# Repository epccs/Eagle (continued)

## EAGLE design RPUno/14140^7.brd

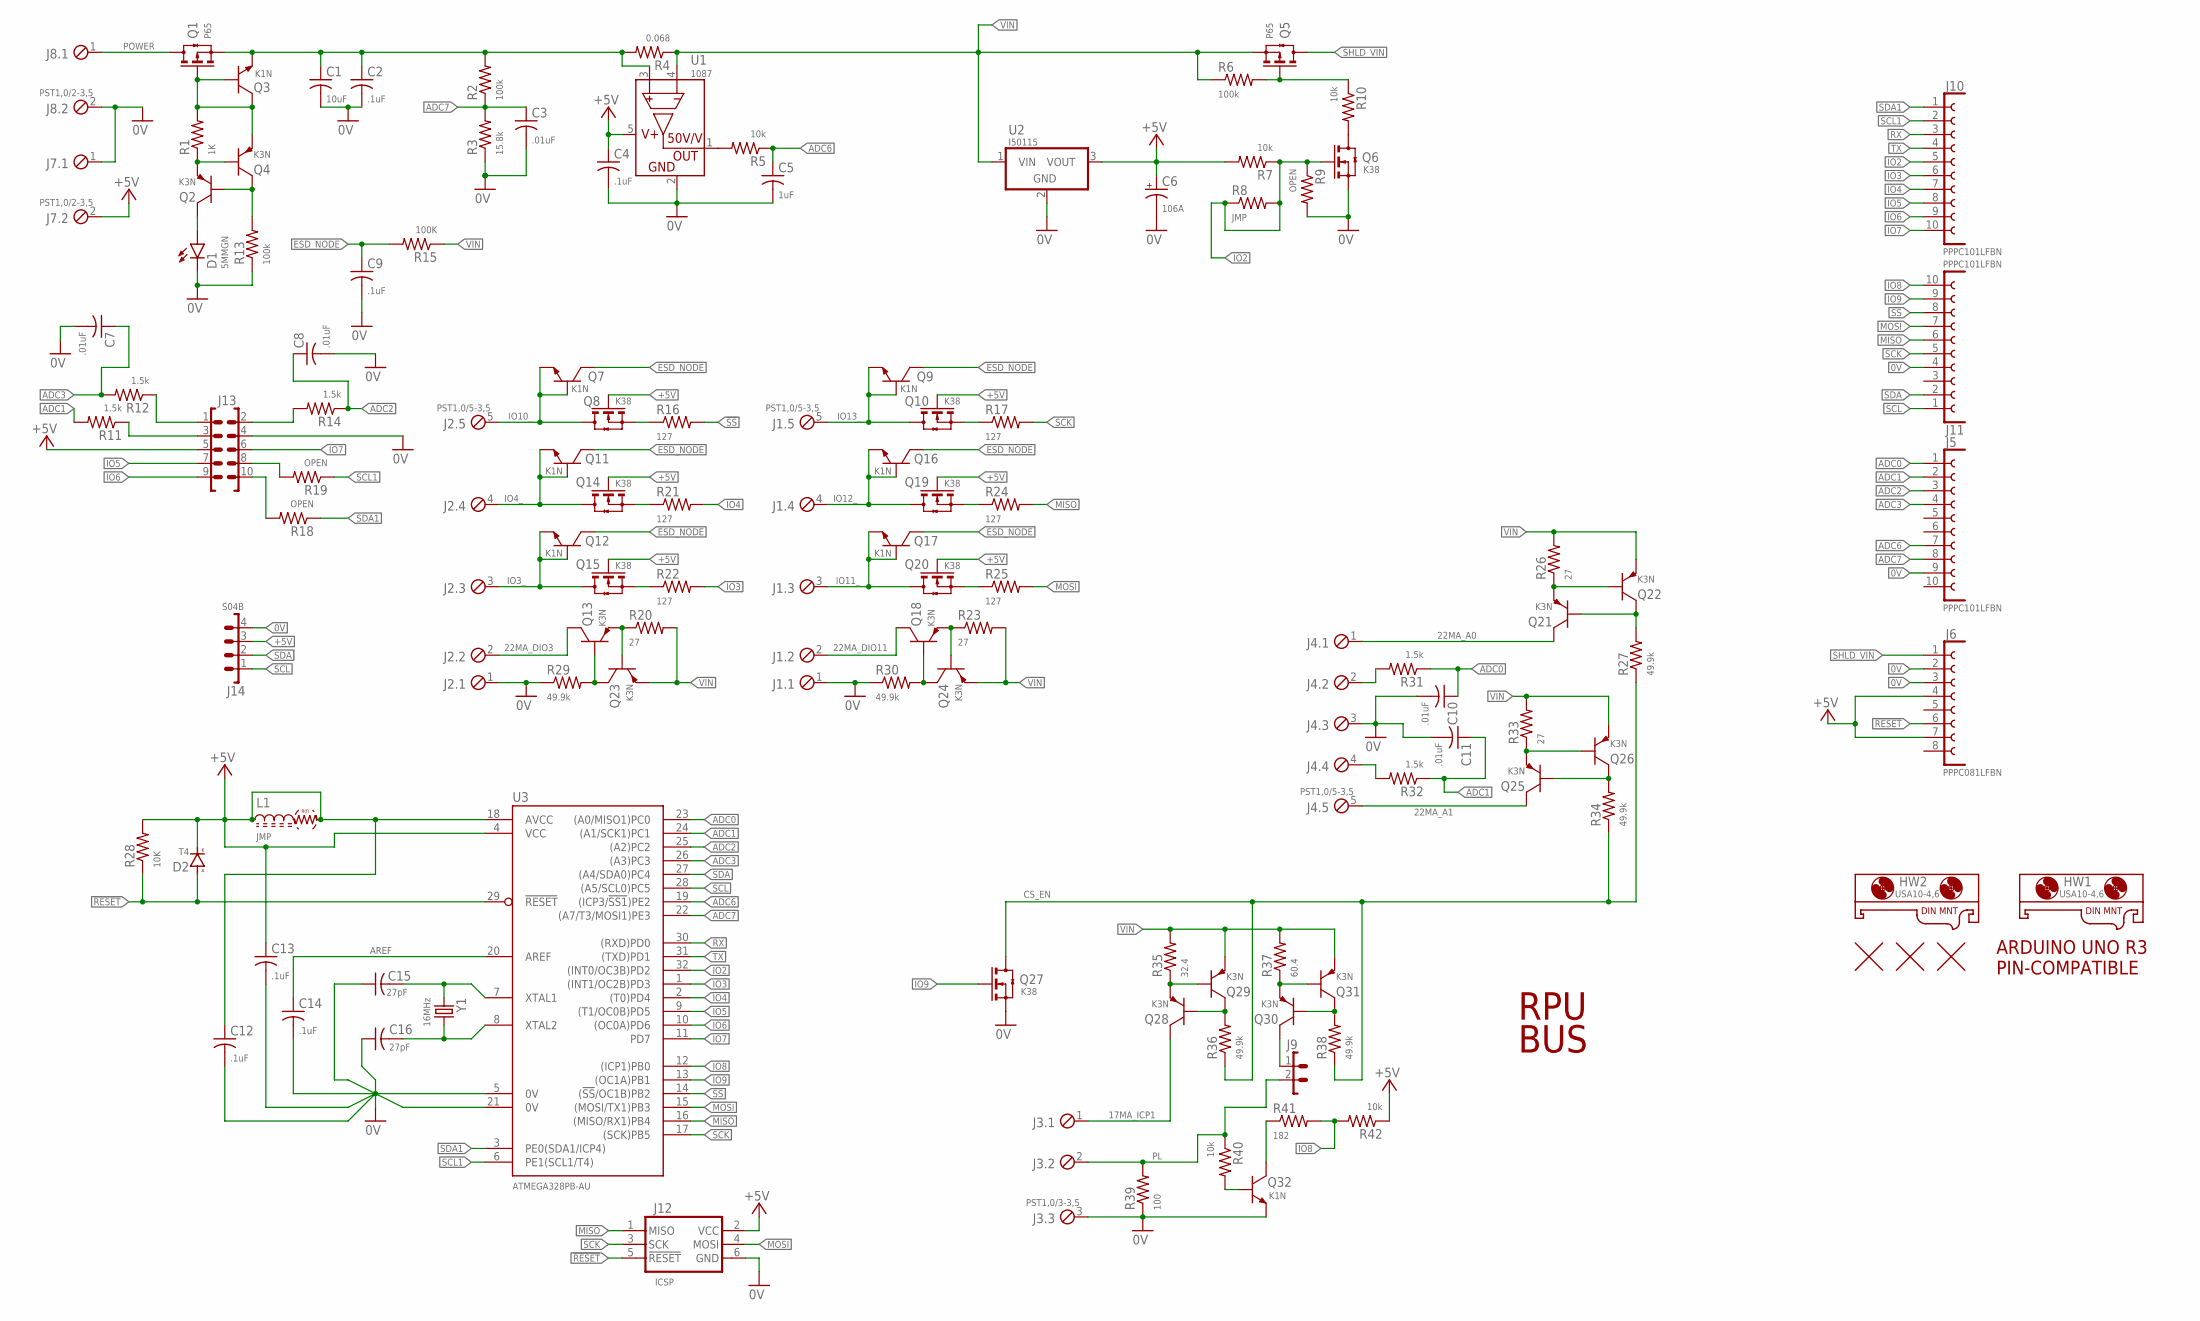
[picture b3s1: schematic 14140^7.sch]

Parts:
C1: 10uF; C1206(3216)
C2: .1uF; C0805(2012)
C3, C7, C8, C10, C11: .01uF; C0603(1608)
C4, C9, C12, C13, C14: .1uF; C0603(1608)
C5: 1uF; C0805(2012)
C6: 106A; 3216
C15, C16: 27pF; C0603(1608)
D1: 5MMGN; LED5MM
D2: T4; SOD123
HW1, HW2: USA10-4,6; USA10
J1, J2, J4: PST1,0/5-3,5; MCV5
J3: PST1,0/3-3,5; MCV3
J5, J10, J11: PPPC101LFBN; F1X10
J6: PPPC081LFBN; F1X8
J7, J8: PST1,0/2-3,5; MCV2
J9: 1X2
J12: ICSP; ISP
J13: 2X5
J14: S04B; B04B
L1: JMP; C0805(2012)
Q1, Q5: P65; SOT23
Q2, Q4, Q13, Q18, Q21, Q22, Q23, Q24, Q25, Q26, Q28, Q29, Q30, Q31: K3N; SOT23
Q3, Q7, Q9, Q11, Q12, Q16, Q17, Q32: K1N; SOT23
Q6, Q8, Q10, Q14, Q15, Q19, Q20, Q27: K38; SOT23
R1: 1K; C0805(2012)
R2, R6, R13: 100k; C0805(2012)
R3: 15.8k; C0805(2012)
R4: 0.068; C1210(3225)
R5, R7, R10, R40, R42: 10k; C0805(2012)
R8: JMP; C0805(2012)
R9, R18, R19: OPEN; C0805(2012)
R11, R12, R14, R31, R32: 1.5k; C0805(2012)
R15: 100K; C0805(2012)
R16, R17, R21, R22, R24, R25: 127; C0805(2012)
R20, R23, R26, R33: 27; C0805(2012)
R27, R29, R30, R34, R36, R38: 49.9k; C0805(2012)
R28: 10K; C0805(2012)
R35: 32.4; C0805(2012)
R37: 60.4; C0805(2012)
R39: 100; C0805(2012)
R41: 182; C0805(2012)
U1: 1087; SOT23-5
U2: I50115; OKI-78SR-H
U3: ATMEGA328PB-AU; TQFP32-08
U$1: ARDUINO-UNO; ARDUINO_UNO
U$2, U$3, U$4: FIDUCIAL1.27; FIDUCIAL-1.27
Y1: 16MHz; CSM-3X

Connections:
0V: C1.2, C2.2, C3.2, C4.2, C5.2, C6.-, C7.2, C8.2, C9.2, C10.2, C11.2, C12.2, C13.2, C14.2, C15.1, C16.1, D1.K, J1.1, J2.1, J3.3, J4.3, J5.9, J6.2, J6.3, J7.1, J8.2, J11.4, J12.6 (GND), J13.4, J14.4, Q6.2(S) (S), Q27.2(S) (S), Q32.E, R3.1, R9.2, R13.1, R29.1, R30.1, R39.1, U1.2 (GND), U2.2 (GND), U3.5 (0V), U3.21 (0V)
17MA_ICP1: J3.1, Q28.C
22MA_A0: J4.1, Q21.C
22MA_A1: J4.5, Q25.C
22MA_DIO3: J2.2, Q13.C
22MA_DIO11: J1.2, Q18.C
!RESET!: D2.A, J6.6, J12.5 (!RESET), R28.1, U3.29 (!RESET)
!SS: J11.8, R16.2, U3.14 ((!SS!/OC1B)PB2)
+5V: C4.1, C6.+, C12.1, C13.1, D2.C (K), J6.4, J6.7, J7.2, J12.2 (VCC), J13.5, J14.3, L1.1, L1.2, Q8.1(G) (G), Q10.1(G) (G), Q14.1(G) (G), Q15.1(G) (G), Q19.1(G) (G), Q20.1(G) (G), R7.2, R28.2, R42.1, U1.5 (VCC), U2.3 (VOUT), U3.4 (VCC), U3.18 (AVCC)
ADC0: C10.1, J5.1, R31.1, U3.23 ((A0/MISO1)PC0)
ADC1: C11.1, J5.2, R11.2, R32.1, U3.24 ((A1/SCK1)PC1)
ADC2: C8.1, J5.3, R14.1, U3.25 ((A2)PC2)
ADC3: C7.1, J5.4, R12.2, U3.26 ((A3)PC3)
ADC6: C5.1, J5.7, R5.1, U3.19 ((ICP3/!SS1!)PE2)
ADC7: C3.1, J5.8, R2.1, R3.2, U3.22 ((A7/T3/MOSI1)PE3)
AREF: C14.1, U3.20 (AREF)
CS_EN: Q27.3(D) (D), R27.1, R34.1, R36.1, R38.1
EN_LD1: J13.8, R19.2
ESD_NODE: C9.1, Q7.C, Q9.C, Q11.C, Q12.C, Q16.C, Q17.C, R15.2
IO2: J10.5, Q6.1(G) (G), R7.1, R8.1, R8.2, R9.1, U3.32 ((INT0/OC3B)PD2)
IO3: J10.6, R22.2, U3.1 ((INT1/OC2B)PD3)
IO3_: J2.3, Q12.B, Q12.E, Q15.3(D) (D)
IO4: J10.7, R21.2, U3.2 ((T0)PD4)
IO4_: J2.4, Q11.B, Q11.E, Q14.3(D) (D)
IO5: J10.8, J13.7, U3.9 ((T1/OC0B)PD5)
IO6: J10.9, J13.9, U3.10 ((OC0A)PD6)
IO7: J10.10, J13.6, U3.11 (PD7)
IO8: J11.10, R41.2, R42.2, U3.12 ((ICP1)PB0)
IO9: J11.9, Q27.1(G) (G), U3.13 ((OC1A)PB1)
IO10_: J2.5, Q7.B, Q7.E, Q8.3(D) (D)
IO11_: J1.3, Q17.B, Q17.E, Q20.3(D) (D)
IO12_: J1.4, Q16.B, Q16.E, Q19.3(D) (D)
IO13_: J1.5, Q9.B, Q9.E, Q10.3(D) (D)
MISO: J11.6, J12.1 (MISO), R24.2, U3.16 ((MISO/RX1)PB4)
MOSI: J11.7, J12.4 (MOSI), R25.2, U3.15 ((MOSI/TX1)PB3)
unnamed: Q19.2(S) (S), R24.1
unnamed: Q5.1(G) (G), R6.2, R10.1
unnamed: Q10.2(S) (S), R17.1
unnamed: Q6.3(D) (D), R10.2
unnamed: Q2.B, Q4.C, R13.2
unnamed: Q1.1(G) (G), Q3.B, Q3.C, Q4.E, R1.2
unnamed: D1.A, Q2.C
unnamed: R5.2, U1.1 (OUT)
unnamed: Q18.E, Q24.B, R23.1
unnamed: Q2.E, Q4.B, R1.1
unnamed: Q18.B, Q24.C, R30.2
unnamed: Q20.2(S) (S), R25.1
unnamed: J13.10, R18.2
unnamed: J13.2, R14.2
unnamed: J13.1, R12.1
unnamed: J13.3, R11.1
unnamed: J9.1, Q30.C
unnamed: Q21.E, Q22.B, R26.1
unnamed: Q21.B, Q22.C, R27.2
unnamed: J4.2, R31.2
unnamed: J4.4, R32.2
unnamed: Q25.E, Q26.B, R33.1
unnamed: Q25.B, Q26.C, R34.2
unnamed: Q13.E, Q23.B, R20.1
unnamed: Q14.2(S) (S), R21.1
unnamed: Q13.B, Q23.C, R29.2
unnamed: Q8.2(S) (S), R16.1
unnamed: Q32.B, R40.2
unnamed: Q32.C, R41.1
unnamed: Q15.2(S) (S), R22.1
unnamed: Q28.E, Q29.B, R35.1
unnamed: C15.2, U3.7 (XTAL1), Y1.1
unnamed: C16.2, U3.8 (XTAL2), Y1.2
unnamed: Q28.B, Q29.C, R36.2
unnamed: Q30.E, Q31.B, R37.1
unnamed: Q30.B, Q31.C, R38.2
PL: J3.2, J9.2, R39.2, R40.1
POWER: J8.1, Q1.3(D) (D)
RX: J10.3, U3.30 ((RXD)PD0)
SCK: J11.5, J12.3 (SCK), R17.2, U3.17 ((SCK)PB5)
SCL: J11.1, J14.1, U3.28 ((A5/SCL0)PC5)
SCL1: J10.2, R19.1, U3.6 (PE1(SCL1/T4))
SDA: J11.2, J14.2, U3.27 ((A4/SDA0)PC4)
SDA1: J10.1, R18.1, U3.3 (PE0(SDA1/ICP4))
SHLD_VIN: J6.1, Q5.3(D) (D)
TX: J10.4, U3.31 ((TXD)PD1)
VIN: Q5.2(S) (S), Q22.E, Q23.E, Q24.E, Q26.E, Q29.E, Q31.E, R4.1, R6.1, R15.1, R20.2, R23.2, R26.2, R33.2, R35.2, R37.2, U1.4 (S-), U2.1 (VIN)
VIN_S: C1.1, C2.1, Q1.2(S) (S), Q3.E, R2.2, R4.2, U1.3 (S+)

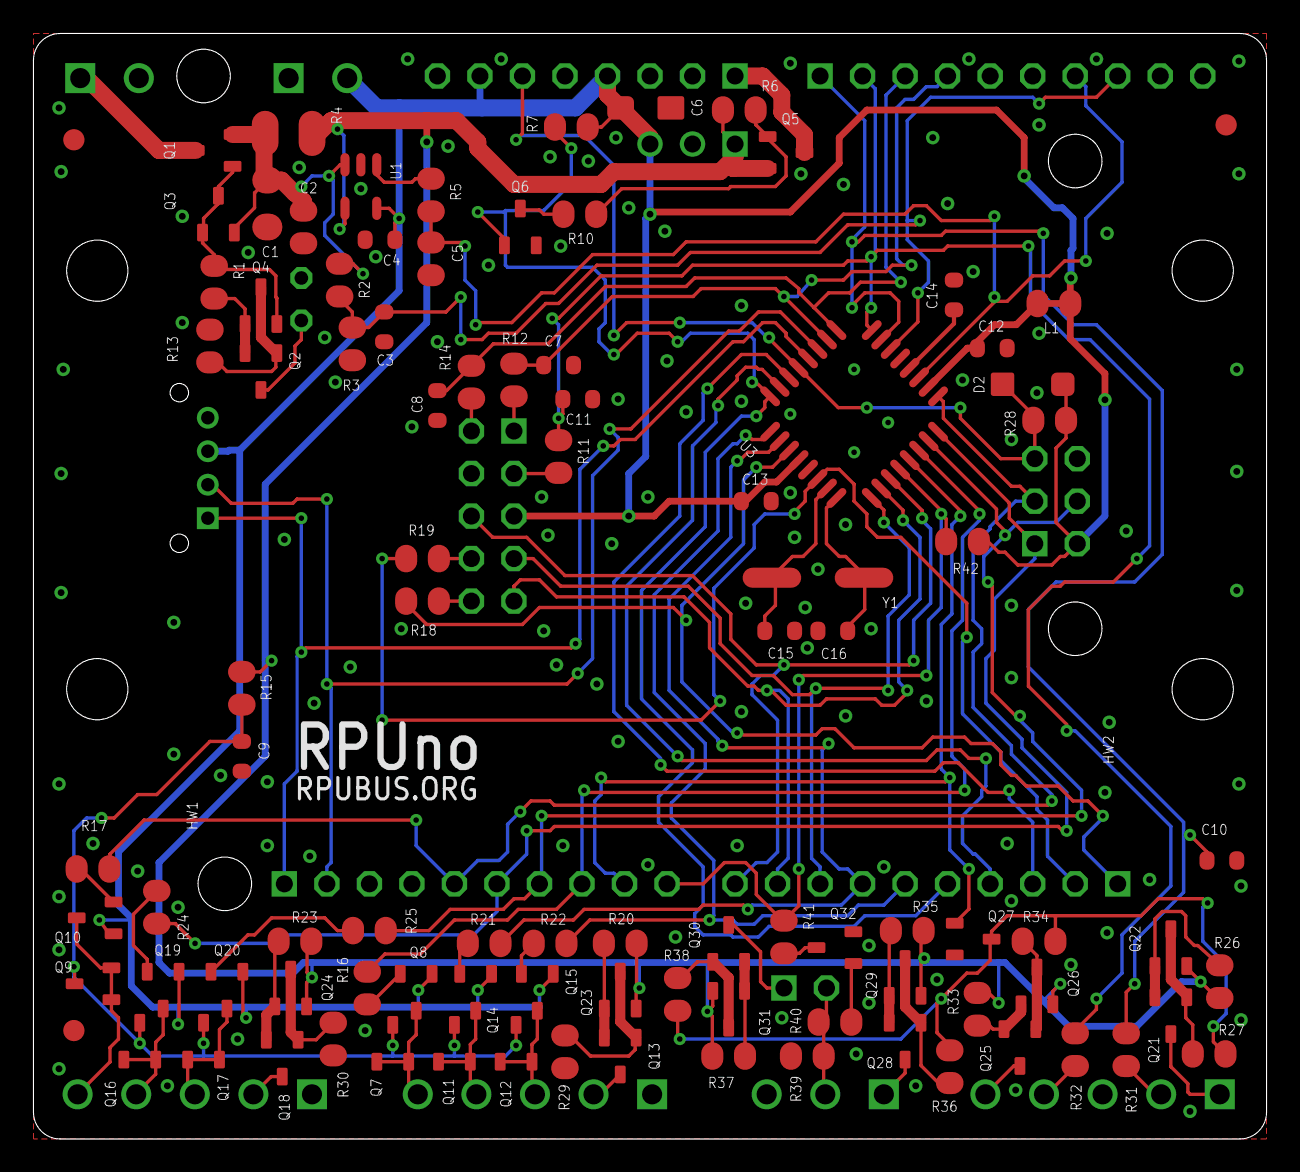
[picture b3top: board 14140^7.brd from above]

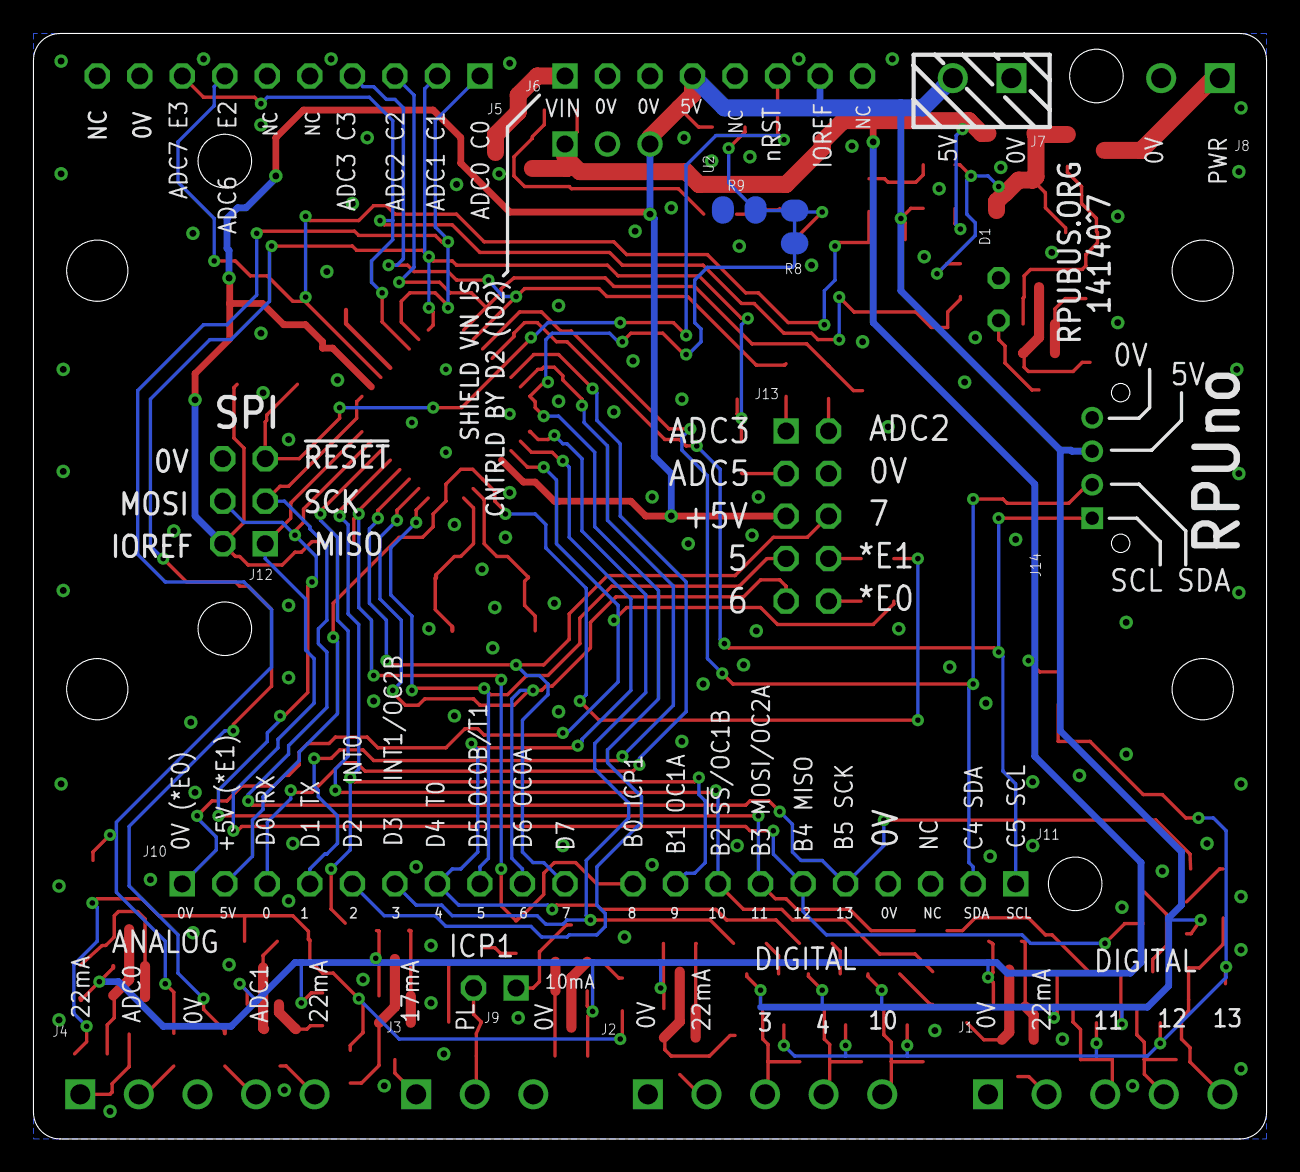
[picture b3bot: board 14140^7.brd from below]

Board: 2 copper layers, 73.7 x 66.0 mm, 117 parts (19 on the bottom side), 83 nets.

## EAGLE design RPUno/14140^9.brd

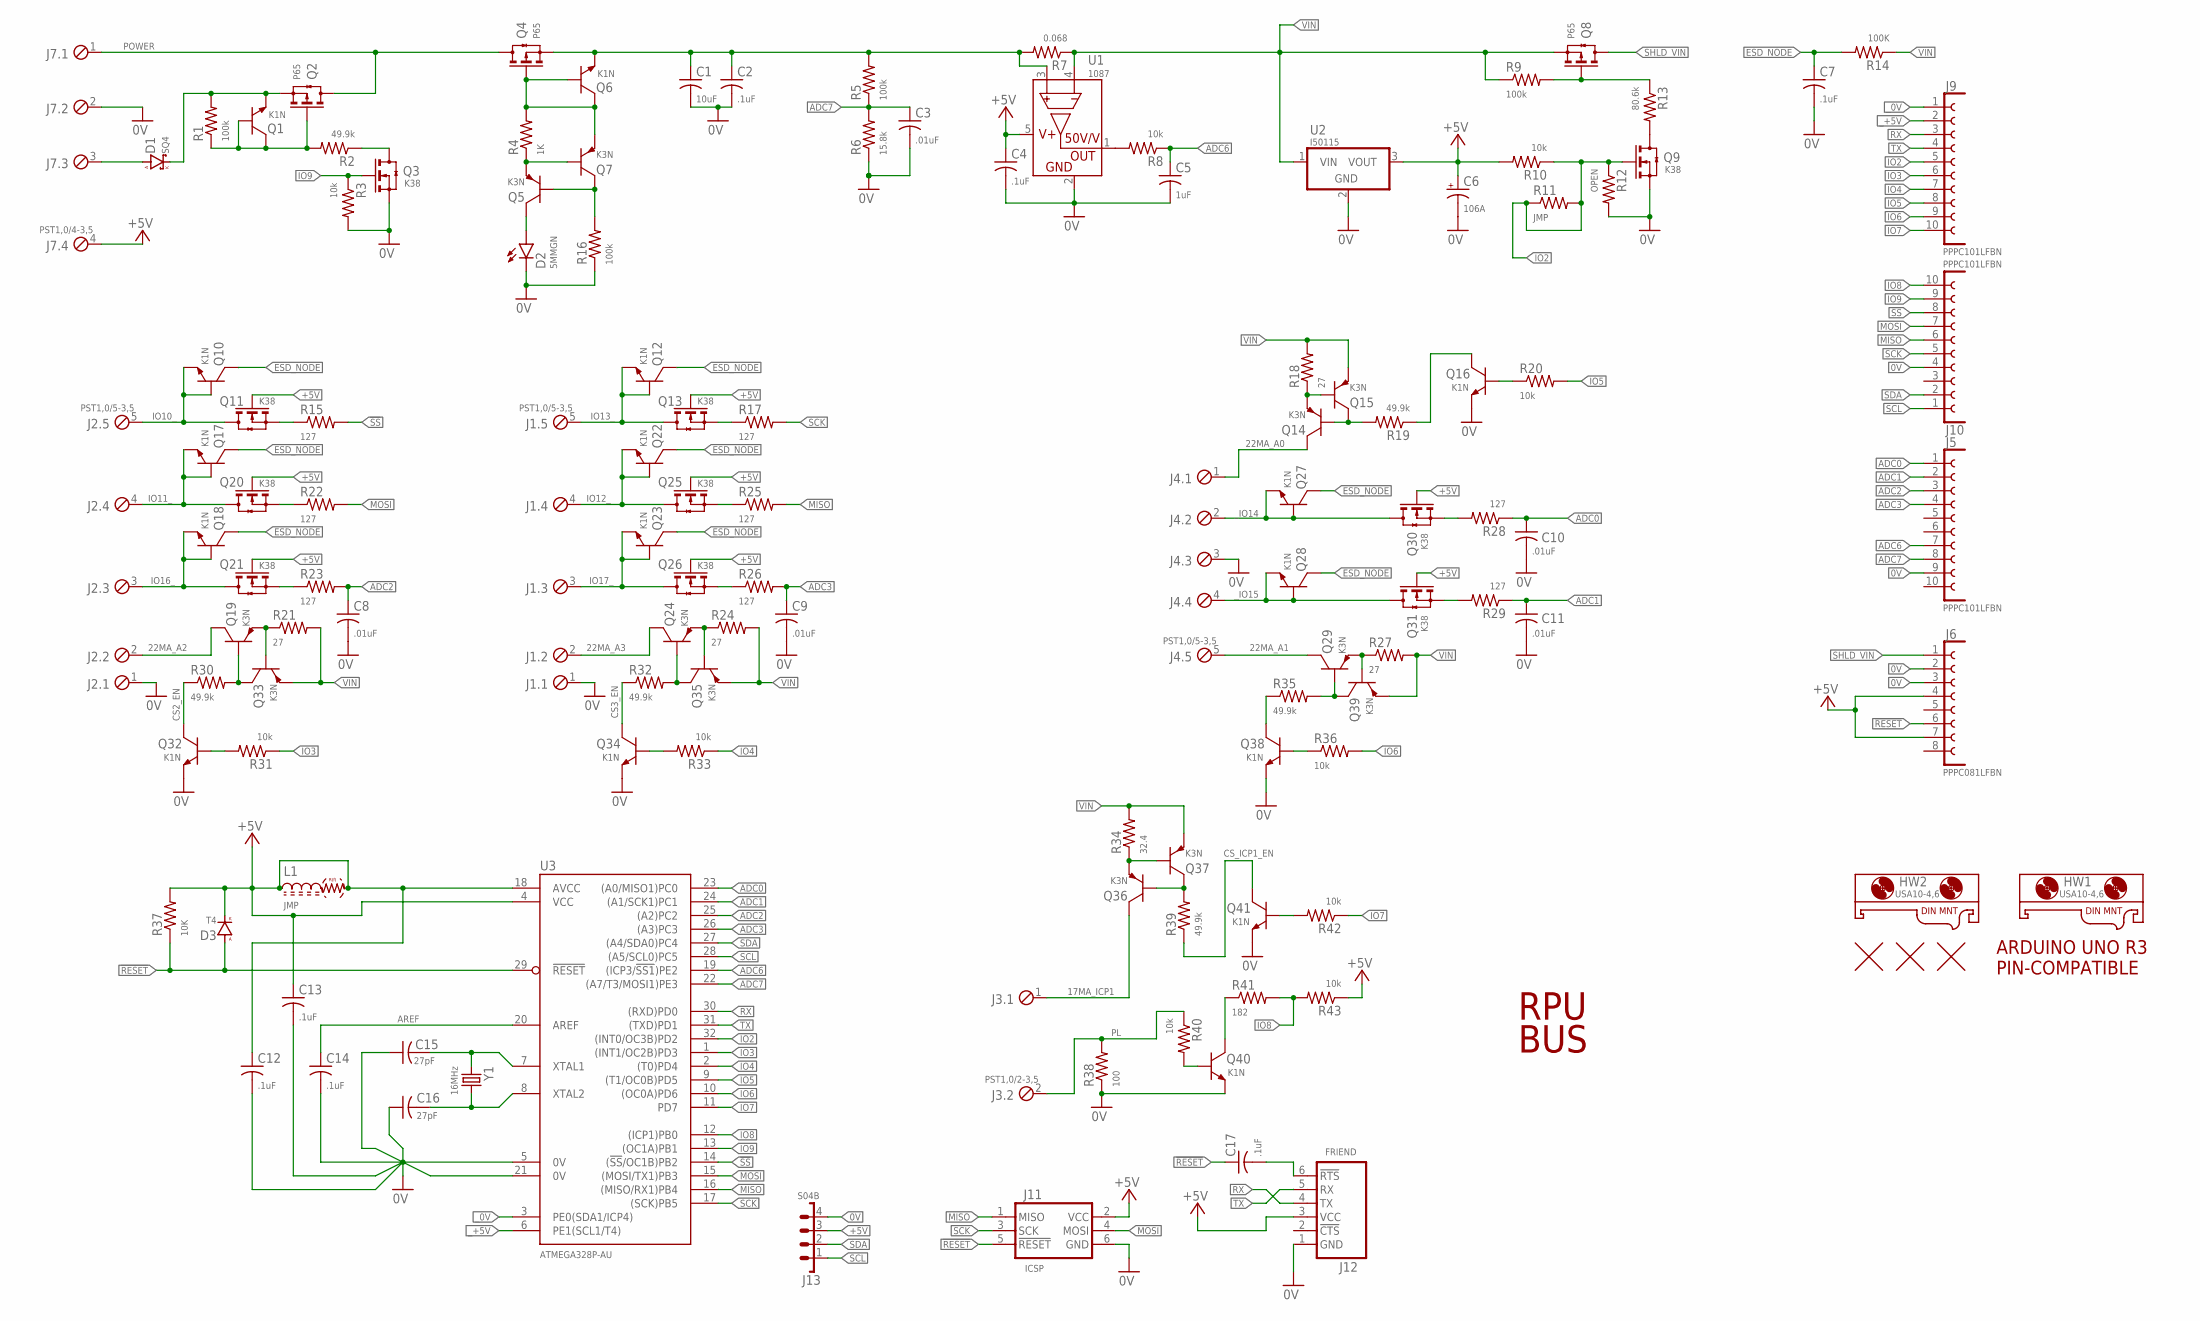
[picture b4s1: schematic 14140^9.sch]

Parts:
C1: 10uF; C1206(3216)
C2: .1uF; C0805(2012)
C3, C8, C9, C10, C11: .01uF; C0603(1608)
C4, C7, C12, C13, C14, C17: .1uF; C0603(1608)
C5: 1uF; C0805(2012)
C6: 106A; 3216
C15, C16: 27pF; C0603(1608)
D1: SQ4; SMA
D2: 5MMGN; LED5MM
D3: T4; SOD123
HW1, HW2: USA10-4,6; USA10
J1, J2, J4: PST1,0/5-3,5; MCV5
J3: PST1,0/2-3,5; MCV2
J5, J9, J10: PPPC101LFBN; F1X10
J6: PPPC081LFBN; F1X8
J7: PST1,0/4-3,5; MCV4
J11: ICSP; ISP
J12: FRIEND
J13: S04B; B04B
L1: JMP; C0805(2012)
Q1, Q6, Q10, Q12, Q16, Q17, Q18, Q22, Q23, Q27, Q28, Q32, Q34, Q38, Q40, Q41: K1N; SOT23
Q2, Q4, Q8: P65; SOT23
Q3, Q9, Q11, Q13, Q20, Q21, Q25, Q26, Q30, Q31: K38; SOT23
Q5, Q7, Q14, Q15, Q19, Q24, Q29, Q33, Q35, Q36, Q37, Q39: K3N; SOT23
R1, R5, R9, R16: 100k; C0805(2012)
R2, R19, R30, R32, R35, R39: 49.9k; C0805(2012)
R3, R8, R10, R20, R31, R33, R36, R40, R42, R43: 10k; C0805(2012)
R4: 1K; C0805(2012)
R6: 15.8k; C0805(2012)
R7: 0.068; C1210(3225)
R11: JMP; C0805(2012)
R12: OPEN; C0805(2012)
R13: 80.6k; C0805(2012)
R14: 100K; C0805(2012)
R15, R17, R22, R23, R25, R26, R28, R29: 127; C0805(2012)
R18, R21, R24, R27: 27; C0805(2012)
R34: 32.4; C0805(2012)
R37: 10K; C0805(2012)
R38: 100; C0805(2012)
R41: 182; C0805(2012)
U1: 1087; SOT23-5
U2: I50115; OKI-78SR-H
U3: ATMEGA328P-AU; TQFP32-08
U$1: ARDUINO-UNO; ARDUINO_UNO
U$2, U$3, U$4: FIDUCIAL1.27; FIDUCIAL-1.27
Y1: 16MHz; CSM-3X

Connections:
0V: C1.2, C2.2, C3.2, C4.2, C5.2, C6.-, C7.2, C8.2, C9.2, C10.2, C11.2, C12.2, C13.2, C14.2, C15.1, C16.1, D2.K, J1.1, J2.1, J4.3, J5.9, J6.2, J6.3, J7.2, J10.4, J11.6 (GND), J12.1 (GND), J13.4, Q3.2(S) (S), Q9.2(S) (S), Q16.E, Q32.E, Q34.E, Q38.E, Q40.E, Q41.E, R3.2, R6.1, R12.2, R16.1, R38.1, U1.2 (GND), U2.2 (GND), U3.5 (0V), U3.21 (0V)
17MA_ICP1: J3.1, Q36.C
22MA_A0: J4.1, Q14.C
22MA_A1: J4.5, Q29.C
22MA_A2: J2.2, Q19.C
22MA_A3: J1.2, Q24.C
!RESET!: C17.1, D3.A, J6.6, J11.5 (!RESET), R37.1, U3.29 (!RESET)
!SS: J10.8, R15.2, U3.14 ((!SS!/OC1B)PB2)
+5V: C4.1, C6.+, C12.1, C13.1, D3.C (K), J6.4, J6.7, J7.4, J11.2 (VCC), J12.3 (VCC), J13.3, L1.1, L1.2, Q11.1(G) (G), Q13.1(G) (G), Q20.1(G) (G), Q21.1(G) (G), Q25.1(G) (G), Q26.1(G) (G), Q30.1(G) (G), Q31.1(G) (G), R10.2, R37.2, R43.1, U1.5 (VCC), U2.3 (VOUT), U3.4 (VCC), U3.18 (AVCC)
ADC0: C10.1, J5.1, R28.1, U3.23 ((A0/MISO1)PC0)
ADC1: C11.1, J5.2, R29.1, U3.24 ((A1/SCK1)PC1)
ADC2: C8.1, J5.3, R23.2, U3.25 ((A2)PC2)
ADC3: C9.1, J5.4, R26.2, U3.26 ((A3)PC3)
ADC6: C5.1, J5.7, R8.1, U3.19 ((ICP3/!SS1!)PE2)
ADC7: C3.1, J5.8, R5.1, R6.2, U3.22 ((A7/T3/MOSI1)PE3)
AREF: C14.1, U3.20 (AREF)
CS2_EN: Q32.C, R30.1
CS3_EN: Q34.C, R32.1
CS_ICP1_EN: Q41.C, R39.1
ESD_NODE: C7.1, Q10.C, Q12.C, Q17.C, Q18.C, Q22.C, Q23.C, Q27.C, Q28.C, R14.2
IO2: J9.5, Q9.1(G) (G), R10.1, R11.1, R11.2, R12.1, U3.32 ((INT0/OC3B)PD2)
IO3: J9.6, R31.1, U3.1 ((INT1/OC2B)PD3)
IO4: J9.7, R33.1, U3.2 ((T0)PD4)
IO5: J9.8, R20.2, U3.9 ((T1/OC0B)PD5)
IO6: J9.9, R36.2, U3.10 ((OC0A)PD6)
IO7: J9.10, R42.1, U3.11 (PD7)
IO8: J10.10, R41.2, R43.2, U3.12 ((ICP1)PB0)
IO9: J10.9, Q3.1(G) (G), R3.1, U3.13 ((OC1A)PB1)
IO10_: J2.5, Q10.B, Q10.E, Q11.3(D) (D)
IO11_: J2.4, Q17.B, Q17.E, Q20.3(D) (D)
IO12_: J1.4, Q22.B, Q22.E, Q25.3(D) (D)
IO13_: J1.5, Q12.B, Q12.E, Q13.3(D) (D)
IO16_: J2.3, Q18.B, Q18.E, Q21.3(D) (D)
IO17_: J1.3, Q23.B, Q23.E, Q26.3(D) (D)
MISO: J10.6, J11.1 (MISO), R25.2, U3.16 ((MISO/RX1)PB4)
MOSI: J10.7, J11.4 (MOSI), R22.2, U3.15 ((MOSI/TX1)PB3)
unnamed: Q25.2(S) (S), R25.1
unnamed: Q8.1(G) (G), R9.2, R13.1
unnamed: Q13.2(S) (S), R17.1
unnamed: Q9.3(D) (D), R13.2
unnamed: Q5.B, Q7.C, R16.2
unnamed: Q4.1(G) (G), Q6.B, Q6.C, Q7.E, R4.2
unnamed: D2.A, Q5.C
unnamed: R8.2, U1.1 (OUT)
unnamed: Q24.E, Q35.B, R24.1
unnamed: Q5.E, Q7.B, R4.1
unnamed: Q24.B, Q35.C, R32.2
unnamed: Q26.2(S) (S), R26.1
unnamed: D1.A, J7.3
unnamed: Q31.2(S) (S), R29.2
unnamed: Q30.2(S) (S), R28.2
unnamed: Q41.B, R42.2
unnamed: Q38.C, R35.1
unnamed: Q14.E, Q15.B, R18.1
unnamed: Q16.C, R19.1
unnamed: Q16.B, R20.1
unnamed: Q14.B, Q15.C, R19.2
unnamed: Q38.B, R36.1
unnamed: Q32.B, R31.2
unnamed: Q29.E, Q39.B, R27.1
unnamed: Q29.B, Q39.C, R35.2
unnamed: Q34.B, R33.2
unnamed: D1.K, Q1.E, Q2.2(S) (S), R1.2
unnamed: Q1.B, Q1.C, Q2.1(G) (G), R1.1, R2.2
unnamed: Q3.3(D) (D), R2.1
unnamed: C17.2, J12.6 (!RTS)
unnamed: Q19.E, Q33.B, R21.1
unnamed: Q20.2(S) (S), R22.1
unnamed: Q19.B, Q33.C, R30.2
unnamed: Q11.2(S) (S), R15.1
unnamed: Q40.B, R40.2
unnamed: Q40.C, R41.1
unnamed: Q21.2(S) (S), R23.1
unnamed: Q36.E, Q37.B, R34.1
unnamed: C15.2, U3.7 (XTAL1), Y1.1
unnamed: C16.2, U3.8 (XTAL2), Y1.2
unnamed: Q36.B, Q37.C, R39.2
PL: J3.2, R38.2, R40.1
POWER: J7.1, Q2.3(D) (D), Q4.3(D) (D)
RX: J9.3, J12.4 (TX), U3.30 ((RXD)PD0)
SCK: J10.5, J11.3 (SCK), R17.2, U3.17 ((SCK)PB5)
SCL: J10.1, J13.1, U3.28 ((A5/SCL0)PC5)
SDA: J10.2, J13.2, U3.27 ((A4/SDA0)PC4)
SHLD_VIN: J6.1, Q8.3(D) (D)
TX: J9.4, J12.5 (RX), U3.31 ((TXD)PD1)
VIN: Q8.2(S) (S), Q15.E, Q33.E, Q35.E, Q37.E, Q39.E, R7.1, R9.1, R14.1, R18.2, R21.2, R24.2, R27.2, R34.2, U1.4 (S-), U2.1 (VIN)
VIN_S: C1.1, C2.1, Q4.2(S) (S), Q6.E, R5.2, R7.2, U1.3 (S+)
_0V: J9.1, U3.3 (PE0(SDA1/ICP4))
_+5V: J9.2, U3.6 (PE1(SCL1/T4))
_IO14: J4.2, Q27.B, Q27.E, Q30.3(D) (D)
_IO15: J4.4, Q28.B, Q28.E, Q31.3(D) (D)

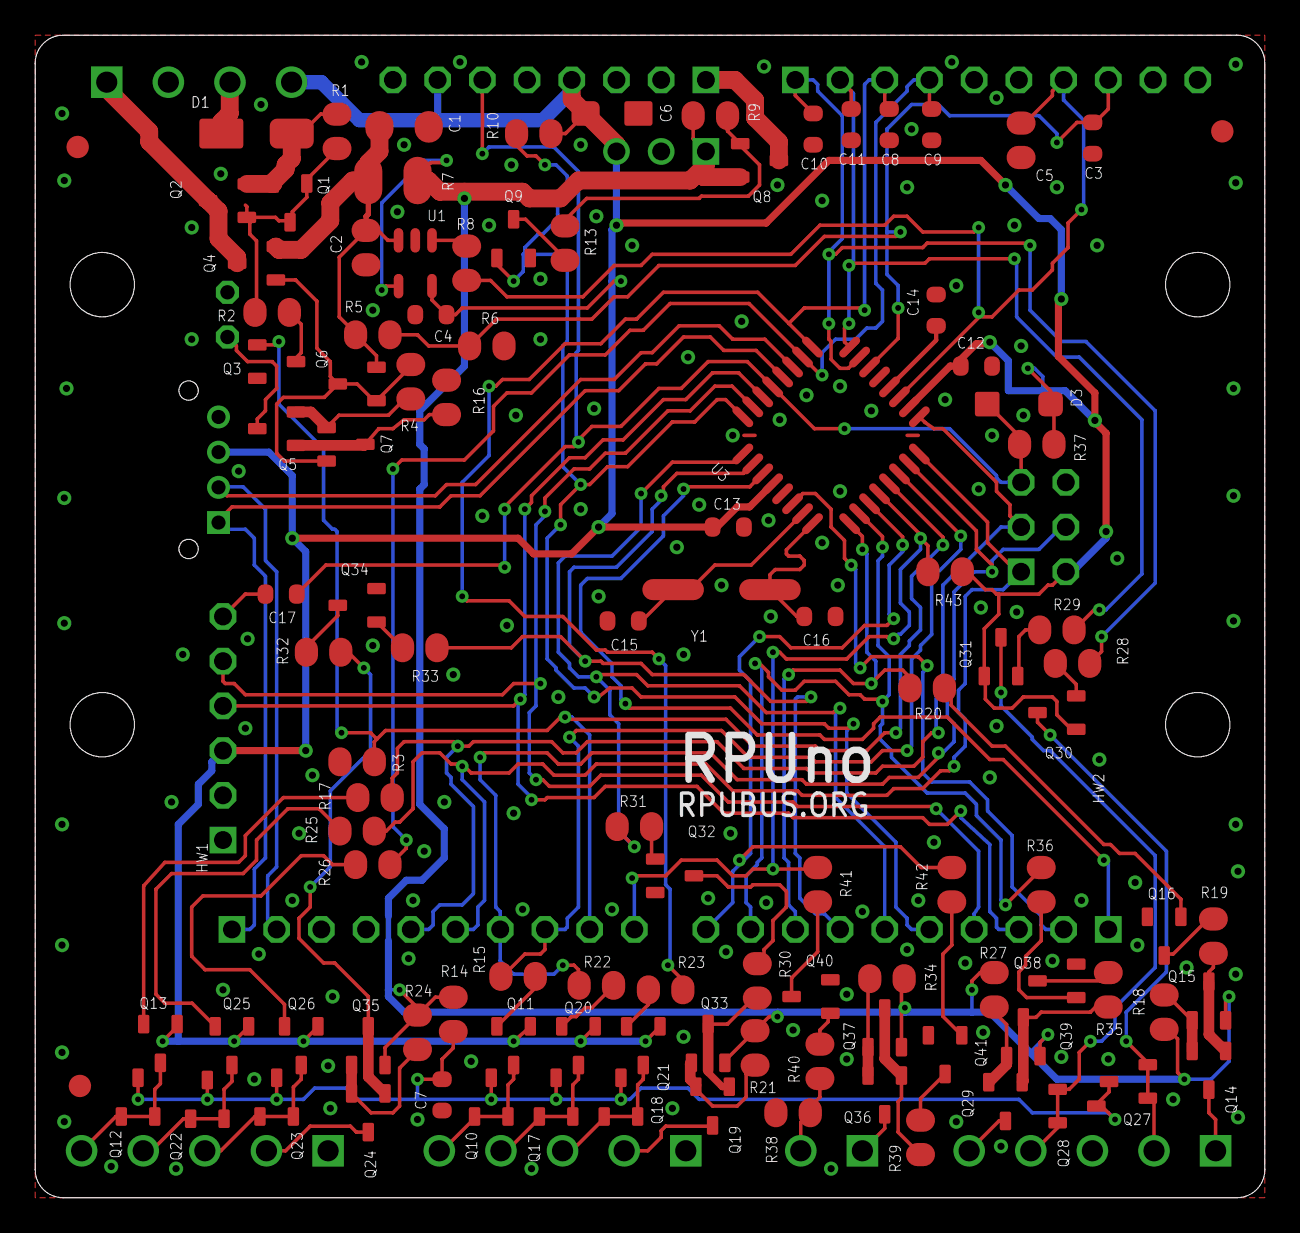
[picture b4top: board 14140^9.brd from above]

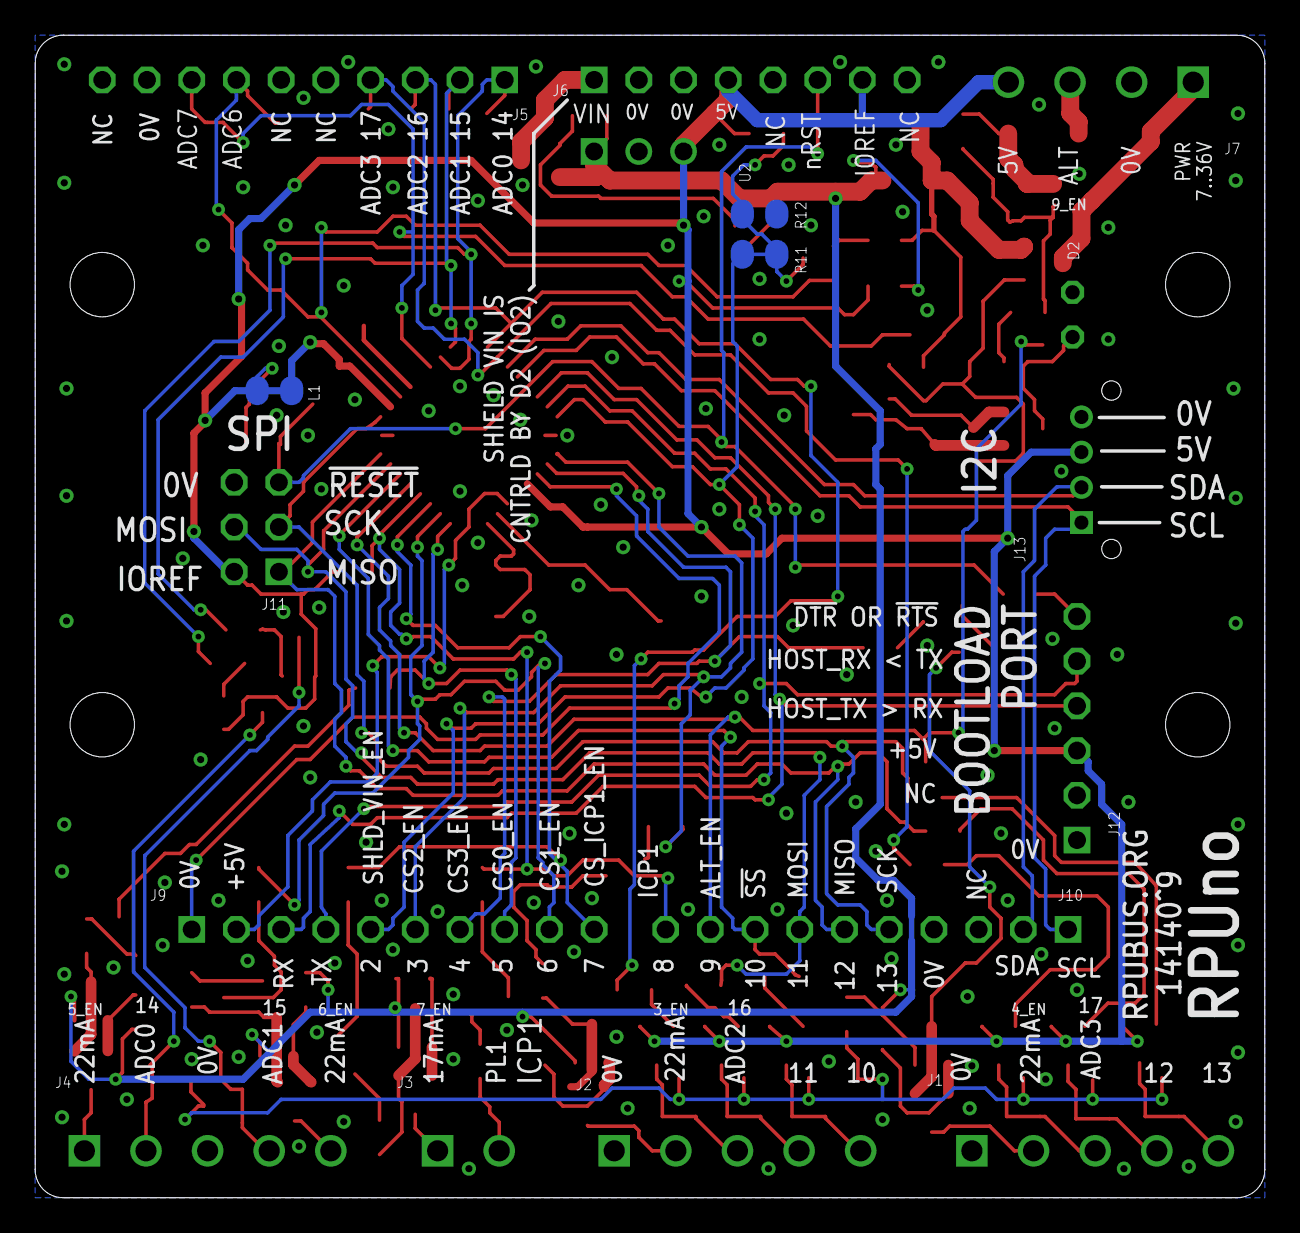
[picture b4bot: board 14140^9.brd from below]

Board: 2 copper layers, 69.8 x 66.0 mm, 127 parts (18 on the bottom side), 91 nets.
